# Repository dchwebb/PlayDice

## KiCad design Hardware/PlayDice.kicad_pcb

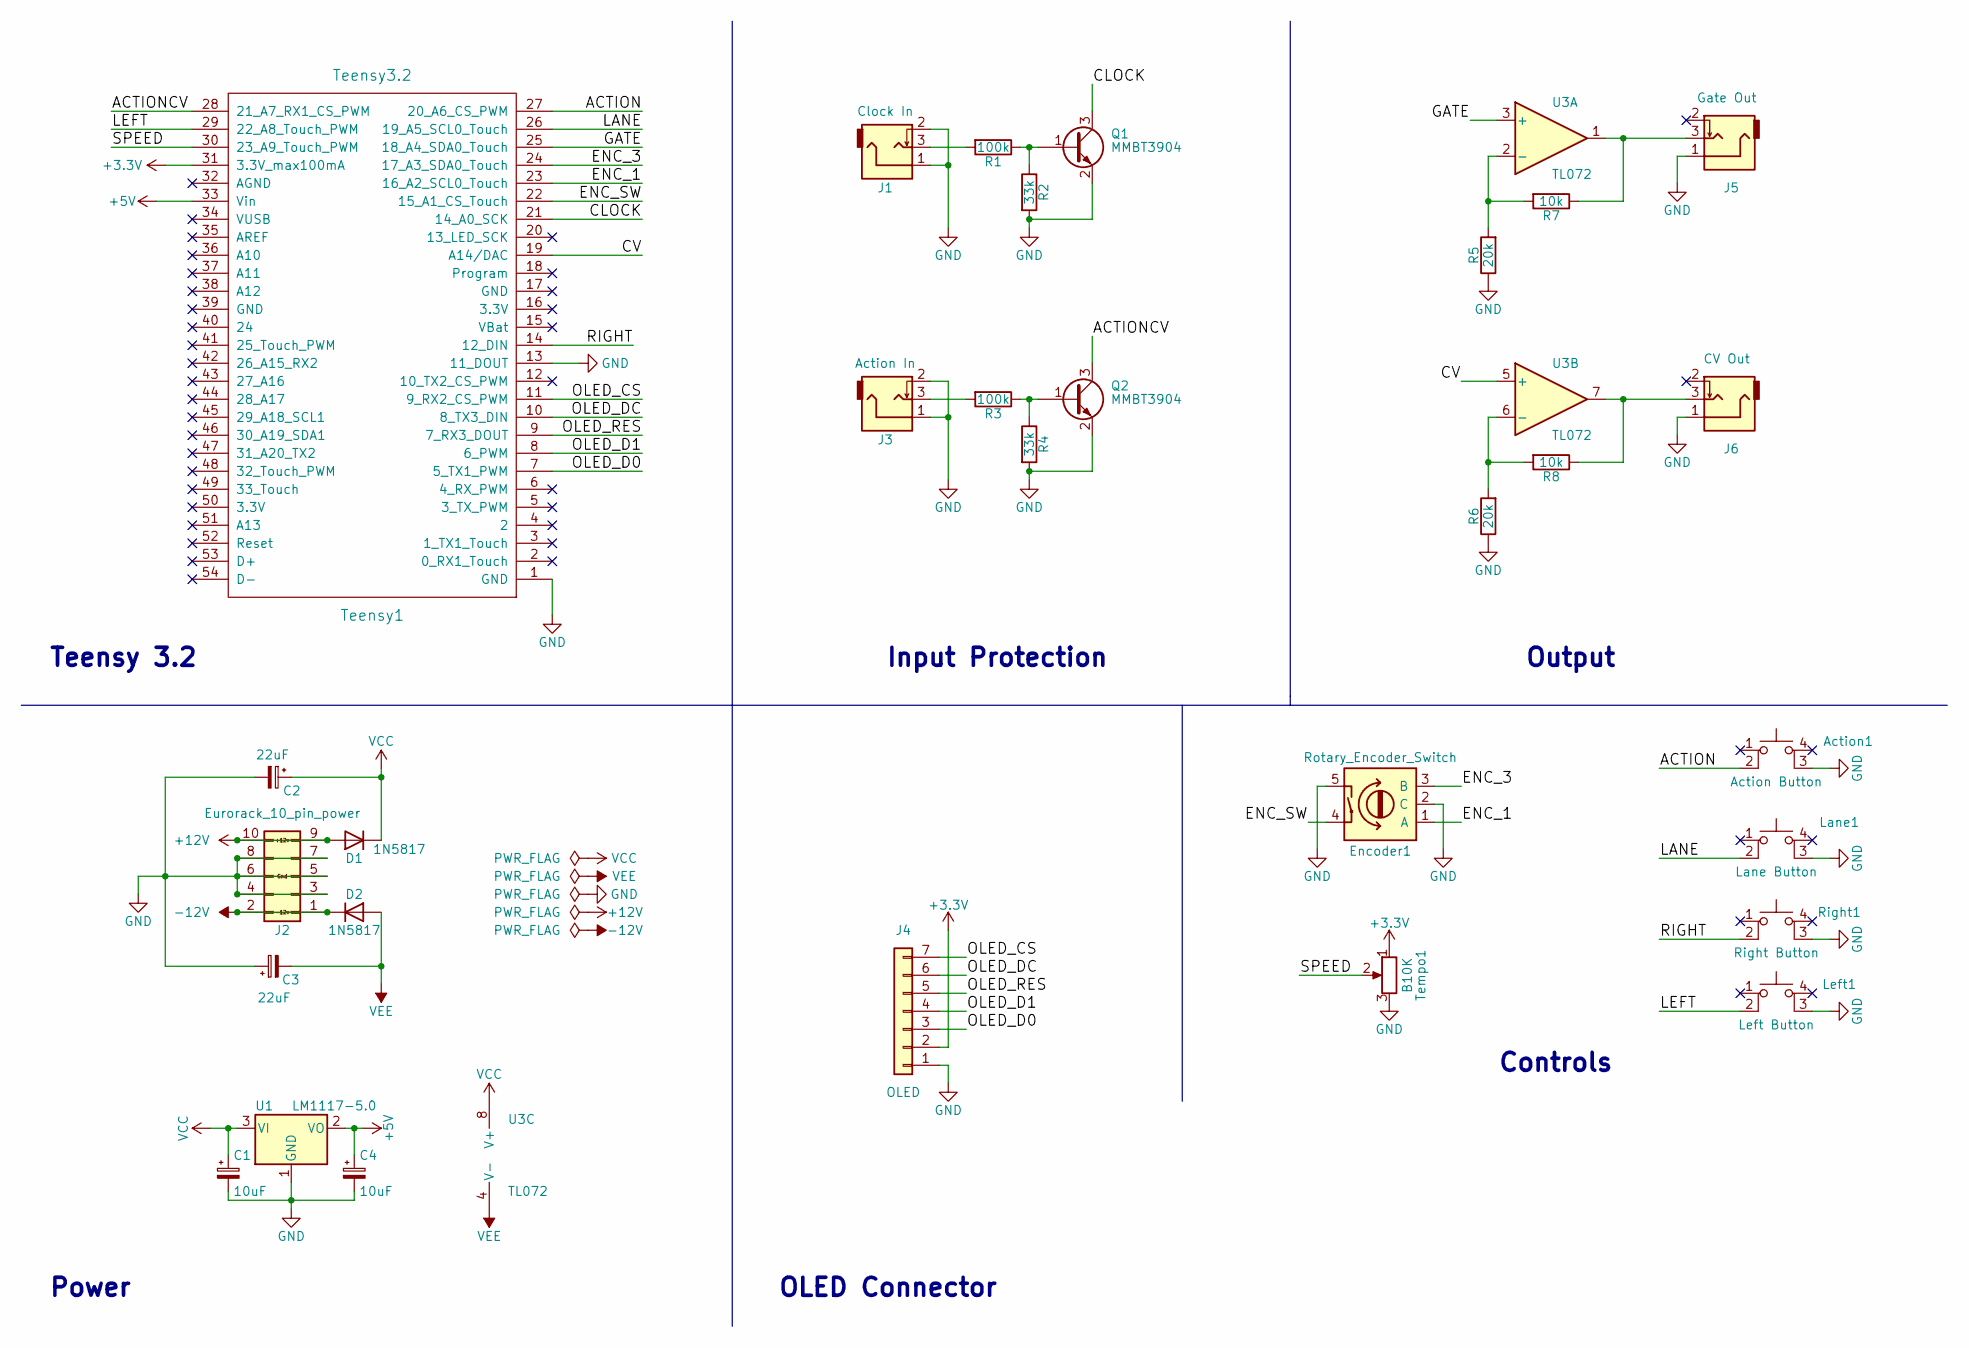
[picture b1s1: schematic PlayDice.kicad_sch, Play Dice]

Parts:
Action1: Action Button; SW_MEC_5GTH9
C1, C4: 10uF; C_0805_2012Metric_Pad1.18x1.45mm_HandSolder
C2, C3: 22uF; CP_Radial_D5.0mm_P2.00mm
D1, D2: 1N5817; D_DO-41_SOD81_P7.62mm_Horizontal
Encoder1: Rotary_Encoder_Switch
J1: Clock In; THONKICONN_hole
J2: Eurorack_10_pin_power; Eurorack_10_pin_header
J3: Action In; THONKICONN_hole
J4: OLED; OLED_7_Pin_Connector
J5: Gate Out; THONKICONN_hole
J6: CV Out; THONKICONN_hole
Lane1: Lane Button; SW_MEC_5GTH9
Left1: Left Button; SW_MEC_5GTH9
Q1, Q2: MMBT3904; SOT-23
R1, R3: 100k; R_0805_2012Metric_Pad1.20x1.40mm_HandSolder
R2, R4: 33k; R_0805_2012Metric_Pad1.20x1.40mm_HandSolder
R5, R6: 20k; R_0805_2012Metric_Pad1.20x1.40mm_HandSolder
R7, R8: 10k; R_0805_2012Metric_Pad1.20x1.40mm_HandSolder
Right1: Right Button; SW_MEC_5GTH9
Teensy1: Teensy3.2; Teensy30_31_32_LC
Tempo1: B10K; Potentiometer_Alps_RK09K_Horizontal
U1: LM1117-5.0; SOT-223
U3: TL072; SOIC-8_3.9x4.9mm_Pitch1.27mm

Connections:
+3V3: J4.2, Teensy1.31 (3.3V_max100mA), Tempo1.1
+5V: C4.1, Teensy1.33 (Vin), U1.2 (VO)
+12V: D1.2 (A), J2.9, J2.10
-12V: D2.1 (K), J2.1, J2.2
/ACTION: Action1.2, Teensy1.27 (20_A6_CS_PWM)
/ACTIONCV: Q2.3 (C), Teensy1.28 (21_A7_RX1_CS_PWM)
/CLOCK: Q1.3 (C), Teensy1.21 (14_A0_SCK)
/CV: Teensy1.19 (A14/DAC), U3.5 (+)
/ENC_1: Encoder1.1 (A), Teensy1.23 (16_A2_SCL0_Touch)
/ENC_3: Encoder1.3 (B), Teensy1.24 (17_A3_SDA0_Touch)
/ENC_SW: Encoder1.4, Teensy1.22 (15_A1_CS_Touch)
/GATE: Teensy1.25 (18_A4_SDA0_Touch), U3.3 (+)
/LANE: Lane1.2, Teensy1.26 (19_A5_SCL0_Touch)
/LEFT: Left1.2, Teensy1.29 (22_A8_Touch_PWM)
/OLED_CS: J4.7, Teensy1.11 (9_RX2_CS_PWM)
/OLED_D0: J4.3, Teensy1.7 (5_TX1_PWM)
/OLED_D1: J4.4, Teensy1.8 (6_PWM)
/OLED_DC: J4.6, Teensy1.10 (8_TX3_DIN)
/OLED_RES: J4.5, Teensy1.9 (7_RX3_DOUT)
/RIGHT: Right1.2, Teensy1.14 (12_DIN)
/SPEED: Teensy1.30 (23_A9_Touch_PWM), Tempo1.2
GND: Action1.3 (K), C1.2, C2.2, C3.1, C4.2, Encoder1.2 (C), Encoder1.5, J1.1, J1.2, J2.3, J2.4, J2.5, J2.6, J2.7, J2.8, J3.1, J3.2, J4.1, J5.1, J6.1, Lane1.3 (K), Left1.3 (K), Q1.2 (E), Q2.2 (E), R2.2, R4.2, R5.1, R6.1, Right1.3 (K), Teensy1.1 (GND), Teensy1.13 (11_DOUT), Tempo1.3, U1.1 (GND)
unnamed: J1.3, R1.2
unnamed: J3.3, R3.2
unnamed: J5.3, R7.1, U3.1
unnamed: J6.3, R8.1, U3.7
unnamed: Q1.1 (B), R1.1, R2.1
unnamed: Q2.1 (B), R3.1, R4.1
unnamed: R5.2, R7.2, U3.2 (-)
unnamed: R6.2, R8.2, U3.6 (-)
VCC: C1.1, C2.1, D1.1 (K), U1.3 (VI), U3.8 (V+)
VEE: C3.2, D2.2 (A), U3.4 (V-)

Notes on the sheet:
Teensy 3.2
Power
OLED Connector
Input Protection
Controls
Output

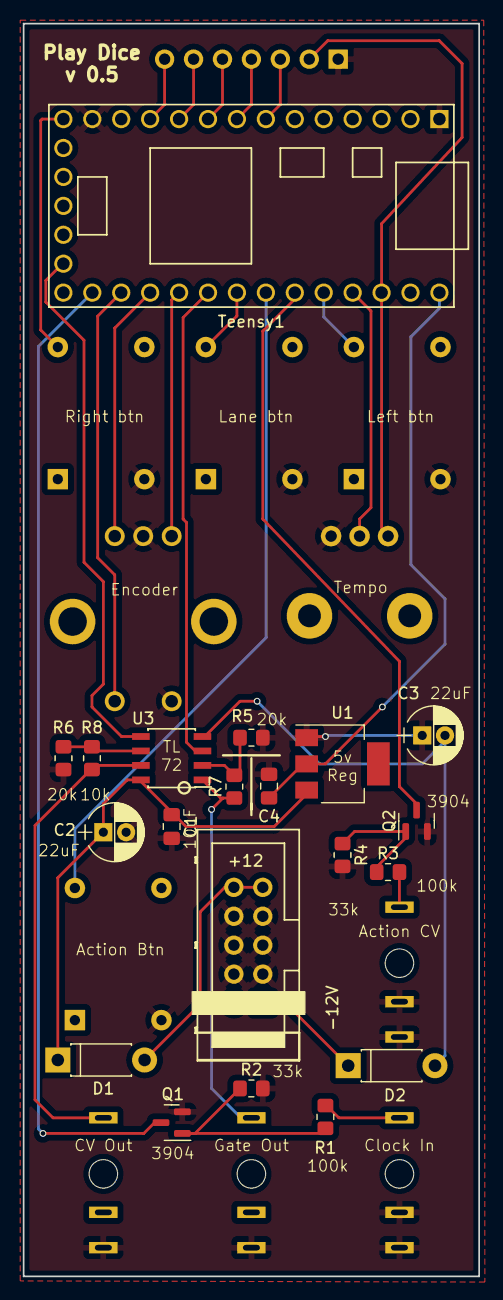
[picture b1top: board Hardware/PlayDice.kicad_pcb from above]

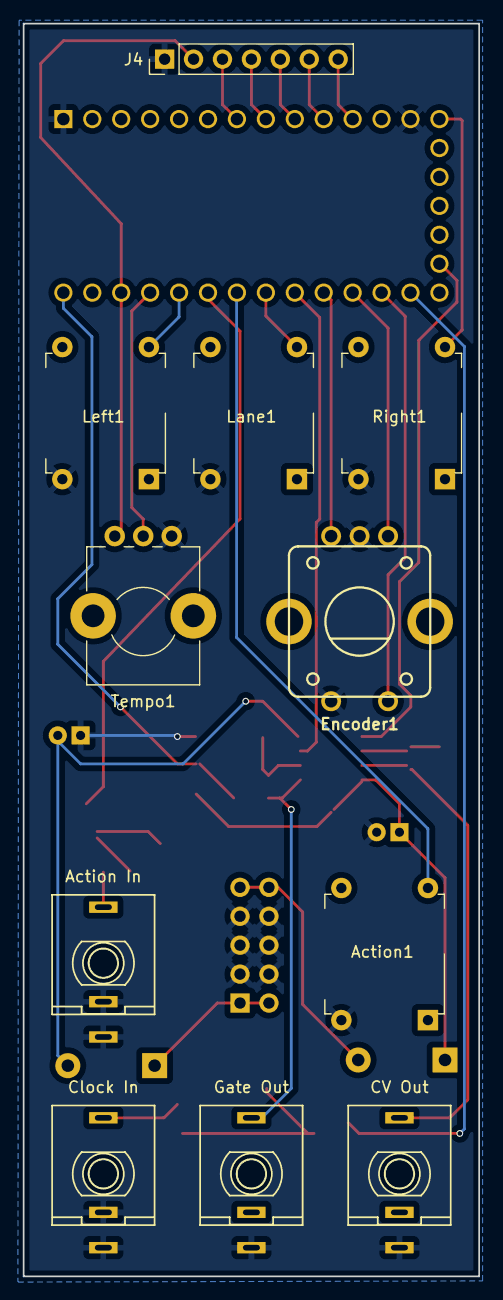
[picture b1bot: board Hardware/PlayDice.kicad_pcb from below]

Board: 2 copper layers, 40.0 x 110.0 mm, 31 parts (11 on the bottom side), 32 nets.

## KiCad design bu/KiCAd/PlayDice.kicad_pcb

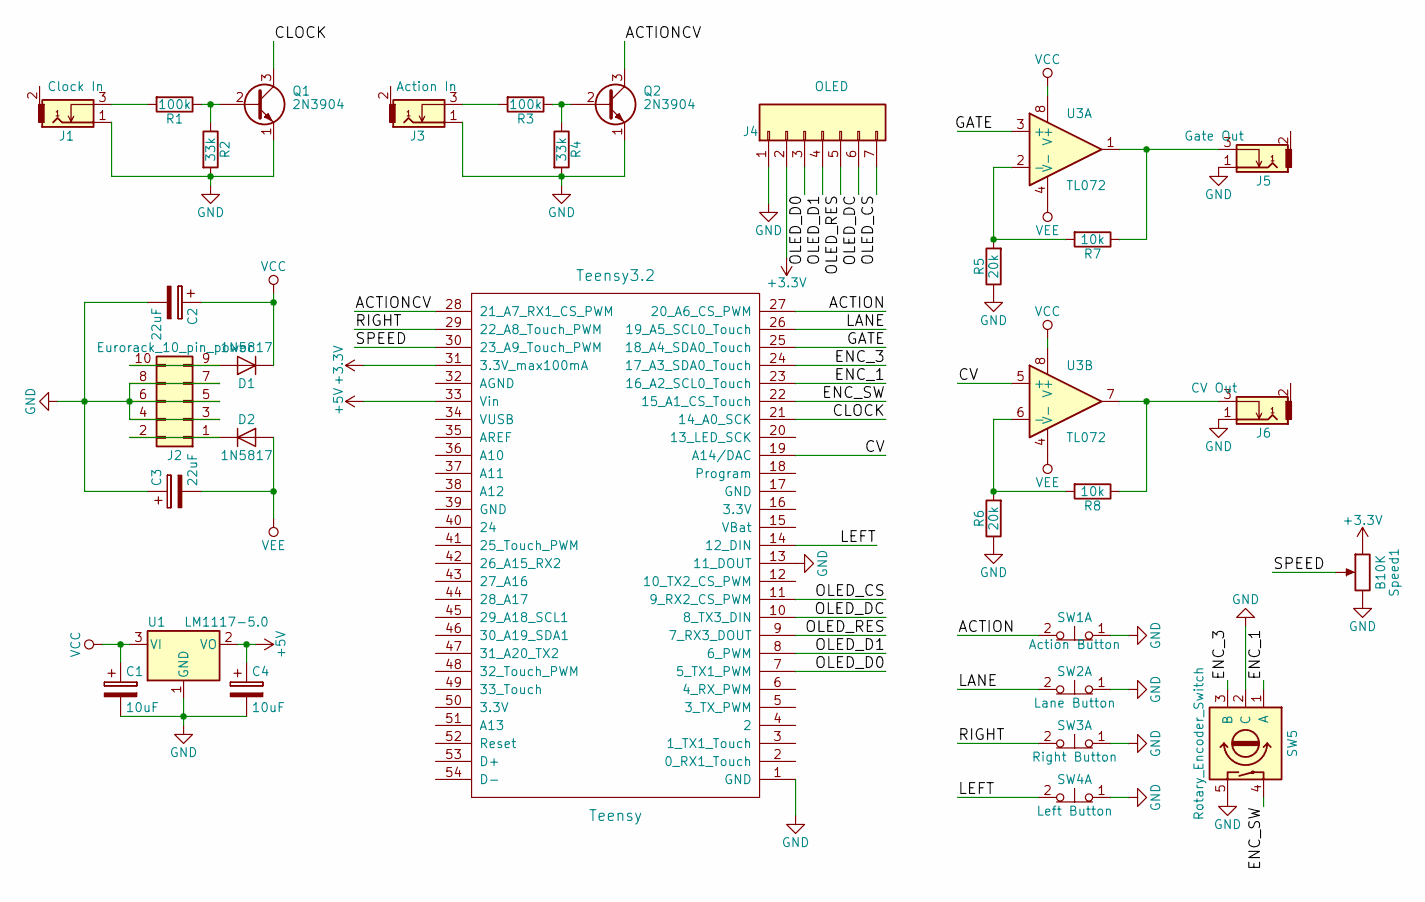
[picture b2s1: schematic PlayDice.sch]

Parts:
C1, C4: 10uF; CP_Radial_D5.0mm_P2.00mm
C2, C3: 22uF; CP_Radial_D5.0mm_P2.00mm
D1, D2: 1N5817; D_DO-41_SOD81_P7.62mm_Horizontal
J1: Clock In; THONKICONN
J2: Eurorack_10_pin_power; Multicomp_MC9A12-1034_2x05x2.54mm_Straight
J3: Action In; THONKICONN
J4: OLED; OLED_7_Pin_Connector
J5: Gate Out; THONKICONN
J6: CV Out; THONKICONN
Q1, Q2: 2N3904; TO-92_Molded_Narrow
R1: 100k; R_0805_HandSoldering
R2, R4: 33k; R_Axial_DIN0207_L6.3mm_D2.5mm_P10.16mm_Horizontal
R3: 100k; R_Axial_DIN0207_L6.3mm_D2.5mm_P10.16mm_Horizontal
R5, R6: 20k; R_Axial_DIN0207_L6.3mm_D2.5mm_P10.16mm_Horizontal
R7, R8: 10k; R_Axial_DIN0207_L6.3mm_D2.5mm_P10.16mm_Horizontal
SW1: Action Button; SW_MEC_5GTH9
SW2: Lane Button; SW_MEC_5GTH9
SW3: Right Button; SW_MEC_5GTH9
SW4: Left Button; SW_MEC_5GTH9
SW5: Rotary_Encoder_Switch
Speed1: B10K; Potentiometer_Alps_RK09K_Horizontal
Teensy: Teensy3.2; Teensy30_31_32_LC
U1: LM1117-5.0; SOT-223
U3: TL072; SOIC-8_3.9x4.9mm_Pitch1.27mm

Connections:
+3V3: J4.2 (3V3), Speed1.1, Teensy.31 (3.3V_max100mA); also elsewhere on the board
+5V: C4.1, Teensy.33 (Vin), U1.2 (VO); also elsewhere on the board
/ACTION: SW1.2, Teensy.27 (20_A6_CS_PWM); also elsewhere on the board
/ACTIONCV: Q2.3 (C), Teensy.28 (21_A7_RX1_CS_PWM); also elsewhere on the board
/CLOCK: Q1.3 (C), Teensy.21 (14_A0_SCK); also elsewhere on the board
/CV: Teensy.19 (A14/DAC), U3.5 (+); also elsewhere on the board
/ENC_1: SW5.1 (A), Teensy.23 (16_A2_SCL0_Touch); also elsewhere on the board
/ENC_3: SW5.3 (B), Teensy.24 (17_A3_SDA0_Touch); also elsewhere on the board
/ENC_SW: SW5.4, Teensy.22 (15_A1_CS_Touch); also elsewhere on the board
/GATE: Teensy.25 (18_A4_SDA0_Touch), U3.3 (+); also elsewhere on the board
/LANE: SW2.2, Teensy.26 (19_A5_SCL0_Touch); also elsewhere on the board
/LEFT: SW4.2, Teensy.14 (12_DIN); also elsewhere on the board
/OLED_CS: J4.7 (CS), Teensy.11 (9_RX2_CS_PWM); also elsewhere on the board
/OLED_D0: J4.3 (D0), Teensy.7 (5_TX1_PWM); also elsewhere on the board
/OLED_D1: J4.4 (D1), Teensy.8 (6_PWM); also elsewhere on the board
/OLED_DC: J4.6 (DC), Teensy.10 (8_TX3_DIN); also elsewhere on the board
/OLED_RES: J4.5 (RES), Teensy.9 (7_RX3_DOUT); also elsewhere on the board
/RIGHT: SW3.2, Teensy.29 (22_A8_Touch_PWM); also elsewhere on the board
/SPEED: Speed1.2, Teensy.30 (23_A9_Touch_PWM); also elsewhere on the board
GND: C1.2, C2.2, C3.1, C4.2, J1.1, J2.3, J2.4, J2.5, J2.6, J2.7, J2.8, J3.1, J4.1 (GND), J5.1, J6.1, Q1.1 (E), Q2.1 (E), R2.2, R4.2, R5.1, R6.1, SW1.1, SW2.1, SW3.1, SW4.1, SW5.2 (C), SW5.5, Speed1.3, Teensy.1 (GND), Teensy.13 (11_DOUT), U1.1 (GND); also elsewhere on the board
unnamed: D1.2 (A), J2.9, J2.10
unnamed: D2.1 (K), J2.1, J2.2
unnamed: J1.3, R1.2
unnamed: J3.3, R3.2
unnamed: J5.3, R7.1, U3.1
unnamed: J6.3, R8.1, U3.7
unnamed: Q1.2 (B), R1.1, R2.1
unnamed: Q2.2 (B), R3.1, R4.1
unnamed: R5.2, R7.2, U3.2 (-)
unnamed: R6.2, R8.2, U3.6 (-)
VCC: C1.1, C2.1, D1.1 (K), U1.3 (VI), U3.8 (V+)
VEE: C3.2, D2.2 (A), U3.4 (V-)

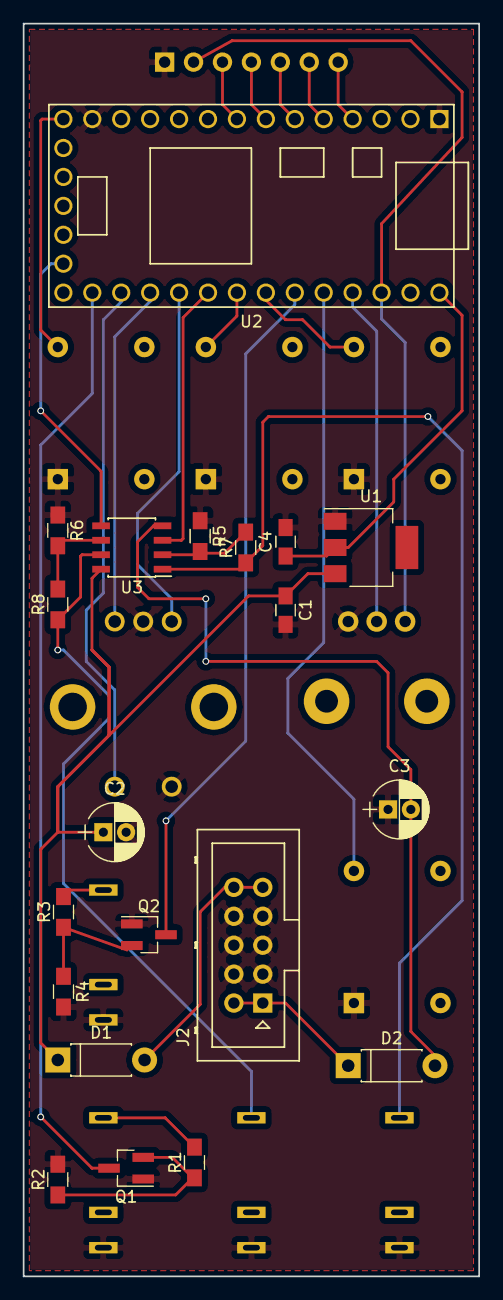
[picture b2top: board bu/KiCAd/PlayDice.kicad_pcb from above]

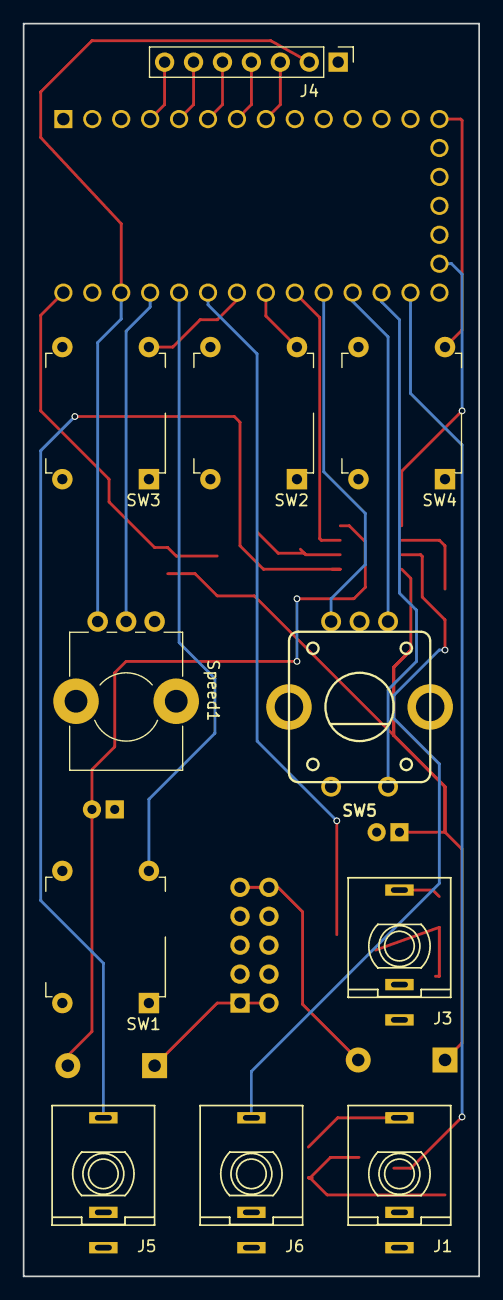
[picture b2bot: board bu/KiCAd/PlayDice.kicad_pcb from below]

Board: 2 copper layers, 40.0 x 110.0 mm, 31 parts (11 on the bottom side), 32 nets.

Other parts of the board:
U2: Teensy3.2; Teensy30_31_32_LC

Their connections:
+3V3: U2.31; also elsewhere on the board
+5V: U2.33; also elsewhere on the board
/ACTION: U2.29; also elsewhere on the board
/ACTIONCV: U2.28; also elsewhere on the board
/CLOCK: U2.21; also elsewhere on the board
/CV: U2.19; also elsewhere on the board
/ENC_1: U2.23; also elsewhere on the board
/ENC_3: U2.24; also elsewhere on the board
/ENC_SW: U2.22; also elsewhere on the board
/GATE: U2.25; also elsewhere on the board
/LANE: U2.26; also elsewhere on the board
/LEFT: U2.14; also elsewhere on the board
/OLED_CS: U2.4; also elsewhere on the board
/OLED_D0: U2.8; also elsewhere on the board
/OLED_D1: U2.7; also elsewhere on the board
/OLED_DC: U2.5; also elsewhere on the board
/OLED_RES: U2.6; also elsewhere on the board
/RIGHT: U2.27; also elsewhere on the board
/SPEED: U2.30; also elsewhere on the board
GND: U2.1, U2.13; also elsewhere on the board

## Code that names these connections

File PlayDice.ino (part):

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uint8_t cvStutterStep;			// if a step is in stutter mode store the count of the current stutters 
uint8_t gateStutterStep;		// if a step is in stutter mode store the count of the current stutters 
uint8_t cvSeqNo = 0;			// store the sequence number for CV patterns
uint8_t gateSeqNo = 0;			// store the sequence number for Gate patterns
uint8_t cvLoopFirst = 0;		// first sequence in loop
uint8_t cvLoopLast = 0;			// last sequence in loop
uint8_t gateLoopFirst = 0;		// first sequence in loop
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boolean pause;					// if true pause sequencers
boolean actionStutter;			// Stutter triggered by action button
uint8_t stutterStep;			// When stutter is triggered by action button store stutter step number based on current clock speed 
uint8_t actionStutterNo = 8;	// Number of stutter steps when triggered by action button
float lfoX = 1, lfoY = 0;		// LFO parameters for quick Minsky approximation
float lfoSpeed;					// lfoSpeed calculated from tempo pot
float oldLfoSpeed;				// lfoSpeed calculated from tempo pot
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struct GatePatterns gate;
struct QuantiseRange quantiseRange[12];

Btn btns[] = { { STEPDN, 22 },{ STEPUP, 12 },{ ENCODER, 15 },{ CHANNEL, 19 },{ ACTIONBTN, 20 },{ ACTIONCV, 21 } };		// numbers refer to Teensy digital pin numbers

ClockHandler clock(minBPM, maxBPM);
DisplayHandler dispHandler;
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//	}
//#endif

	tempoPot = analogRead(TEMPOPIN);		//  read value of potentiometer to set speed

	// work out whether to get bpm from tempo potentiometer or clock signal (checking that we have recieved a recent clock signal)
	if (clockBPM >= minBPM && clockBPM < maxBPM && clock.hasSignal()) {
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						if (activeSeq == SEQCV) {
							cv.seq[cvSeqNo].steps = constrain(cv.seq[cvSeqNo].steps + (upOrDown ? 1 : -1), 1, 8);
						} else {
							gate.seq[gateSeqNo].steps = constrain(gate.seq[gateSeqNo].steps + (upOrDown ? 1 : -1), 1, 8);
						}
					}

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			gate.seq[seqNum].Steps[s].stutter = round((getRand() * 6) + 1);
		}
		else {
			gate.seq[seqNum].Steps[s].stutter = 0;
		}
	}
}
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
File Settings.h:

#pragma once
#ifndef _SETTINGS_h
#define _SETTINGS_h

#if defined(ARDUINO) && ARDUINO >= 100
	#include "arduino.h"
#else
	#include "WProgram.h"
#endif

#define DEBUGSTEP 0
#define DEBUGCLOCK 0
#define DEBUGRAND 0
#define DEBUGQUANT 0
#define DEBUGBTNS 0
#define DEBUGFRAME 0

#define LED 13
#define CLOCKPIN 14		// incoming voltage clock
#define TEMPOPIN 9		// analog pin 9 - pot for controlling clock manually
#define ENCCLKPIN 16	// encoder pin 1
#define ENCDATAPIN 17	// encoder pin 3
#define GATEOUT 18		// Gate sequence out
#define DACPIN 40		// CV sequence out

#define OLED_CS    9
#define OLED_DC    8
#define OLED_RESET 7
#define OLED_MOSI  6		// D1 on OLED
#define OLED_CLK   5		// D0 on OLED

// edit modes: STEPV voltage; STEPR random level; STUTTER stutter count; PATTERN pattern number; STEPS in pattern; SEQOPTS - randomise settings; SETUP - system menu; LFO/NOISE - lfo or white noise mode
enum editType { STEPV, STEPR, STUTTER, PATTERN, SEQMODE, STEPS, LOOPFIRST, LOOPLAST, SEQOPT, SEQROOT, SEQSCALE, SETUP, SUBMENU, LFO, NOISE };

// action mode - what happens when the action button is pressed
enum actionOpts { ACTSTUTTER, ACTRESTART, ACTPAUSE };

enum seqType { SEQCV, SEQGATE };
enum cvMode { CV, PITCH};
enum gateMode { GATE, TRIGGER };
enum rndType { UPPER, LOWER };

static String const OffOnOpts[] = { "Off", "On" };
String const pitches[] = { "C", "C#", "D", "D#", "E", "F", "F#", "G", "G#", "A", "A#", "B" };
String const scales[] = { "Chromatic", "Major", "Pentatonic", "Harmonic minor", "Melodic minor" };
static boolean scaleNotes[5][12] = { { 1,1,1,1,1,1,1,1,1,1,1,1 },{ 1,0,1,0,1,1,0,1,0,1,0,1 },{ 1,0,0,1,0,1,0,1,0,0,1,0 },{ 1,0,1,1,0,1,0,1,1,0,0,1 },{ 1,0,1,1,0,1,0,1,0,1,0,1 } };
uint8_t const scaleSize = 5;
String const scalesShort[] = { "", "", "p", "h", "m" };
String const actions[] = { "Stutter", "Restart", "Pause" };

enum seqInitType { INITNONE, INITRAND, INITVALS, INITBLANK, INITHIGH, INITMEDIUM, INITLOW };
String const initCVSeq[] = { "None", "All", "Vals", "Blank", "High", "Med", "Low" };
uint8_t const initCVSeqSize = 7;
String const initGateSeq[] = { "None", "All", "Vals", "Blank" };
uint8_t const initGateSeqSize = 4;


// adds or subtracts one from a number, looping back to zero if > max or to max if < 0
#define AddNLoop(x,add,max) ((x)==(max)&&(add)?0:((x)==0&&!(add)?(max):((add)?(x)+1:(x)-1)))


// define structures to store sequence data
struct CvStep {
	float volts;
	uint8_t rand_amt : 4; // from 0 to 10
	uint16_t stutter : 5;
};
struct GateStep {
	uint16_t on : 1;
	uint8_t rand_amt : 4; // from 0 to 10
	uint16_t stutter : 5;
};
struct CvSequence {
	uint8_t steps : 4;		//  Number of steps in sequence
	uint8_t mode : 4;		//	CV or pitch mode
	uint8_t root : 6;
	uint8_t scale : 6;
	struct CvStep Steps[8];
};
struct GateSequence {
	uint8_t steps : 4;		//  Number of steps in sequence
	uint8_t mode : 4;		//	Gate or trigger mode
	struct GateStep Steps[8];
};

struct CvPatterns {
	struct CvSequence seq[8];
};
struct GatePatterns {
	struct GateSequence seq[8];
};


//	state handling for momentary buttons
struct Btn {
	int name;
	int pin;
	boolean pressed;
	boolean released;
	boolean longClick;
	uint32_t lastPressed;
};
enum btnName { STEPUP, STEPDN, ENCODER, CHANNEL, ACTIONBTN, ENCUP, ENCDN, ACTIONCV };

struct MenuItem {
	int pos;
	String name;
	boolean selected;
	String val = "";
};

struct QuantiseRange {
	float to;		// the upper range of voltage included in this quantise step
	float target;	// the voltage to shift the CV to if in this step
};



#endif

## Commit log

2018-03-14 Add .gitignore and .gitattributes.
2018-03-14 14th March
2018-03-15 multiple patterns added
2018-03-20 Gate handling and variable optimisation
2018-03-20 Gate randomisation and display done
2018-03-24 Stutter edit function added; gate out functioning
2018-03-24 Basic stutter functionality
2018-04-14 Optimisations to I2C display routines
2018-04-14 Seq looping and action button
2018-04-25 Button pins moved to free SPI connections
2018-05-01 CV Stutter and SPI implemented
2018-05-01 Fixed sequence selection
2018-05-21 UI refresh every block; Partial UI to change step length
2018-05-22 Different step lengths; pattern randomisation options
2018-06-26 Test Update from new PC
2018-06-26 Action stutter for CV and Gate
2018-06-26 Implemented basic clock divider based on position of tempo pot when clock is present
2018-06-28 Basic LFO mode added
2018-06-29 Implemented LFO Mode
2018-07-08 KiCad files
2018-07-10 Moved Teensy PIns for PCB layout
2018-07-10 Added Kicad files (again)
2018-07-11 Final pin reassignments for PCB
2018-07-12 Added Save/Load Settings functionality
2018-07-12 KiCad
2018-07-12 Kicad2
2018-07-12 test
2018-07-13 sequence saving/loading updated
2018-07-14 Autosave implemented and cleaned up noise mode
2018-07-18 Bug fixes and PCB updates
2018-07-18 Basic pitched CV mode
2018-07-20 Submenu functionality and some pitch mode quantising
2018-07-21 PCB fixed transistor connections; added basic handling for scale quantisation
2018-09-30 Bug fixes
2018-09-30 Bug Fixes and panel updates
2018-10-03 Clock fixes, better debugging
2018-10-03 Fixed random error; added trigger mode for gate sequence
2018-10-05 Added CV offset for calibration; basic pitch and scale quantising
2018-10-08 Bug fixes and code tidy up
2018-10-09 Added per sequence gate/trigger and pitch/cv options
2018-10-11 Improvements to clock handler; added additional scales to quantiser
2018-10-30 Various bug fixes - mainly around quantising
2018-11-30 Various code tidy-ups. Added configuration option for encoder direction. ADded new panel gerbers
2018-11-30 File tidy up
2021-09-18 Removed bu files
2021-09-19 Revised Panel; started transferring Kicad files to v 5.99
2021-09-21 Updated to black and silver colour scheme; Transferred pcb and panel to Kicad 5.99
2021-09-23 Panel pcb gerbers prepared for production
